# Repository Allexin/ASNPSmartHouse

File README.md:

**ЧЕРНОВИК**  
Uart Settings:  
Baud Rate: 19200  
Parity: No Parity  
Stop bit: One Stop  
Data Size: 8 bit  

Используемые типы:  
безнаковый байт - основной тип используемый в пакетах
строка - uint8_t длина строки, массив uint8_t[длина строки]

Структура команды:  
INFO  
ADDRESS  
DATA_LENGTH  
DATA  
CHECKSUM  

INFO - информация о пакете. Биты считаются справа налево.  
1 - бит четности(количество установленных битов должно быть четным)  
2 - бит приоритета(0 - отправляем если можем, 1 - отправляем всегда)  
3 - бит типа адреса(0 - персональный адрес, 1 - групповой адрес)  
4 - бит события(0 -  обычный пакет, 1 - событие)  
5,6,7.8 - не используются.  
ADDRESS - адрес устройства или группы, которому предназначается команда. 0x00 - броадкаст.  Если пакет является событием - адрес должен содержать собственный адрес устройства. Как будто он отправляет пакет самому себе.  
DATA_LENGTH - длина данных. Значение от 1 до 255.  
DATA - данные размером DATA_LENGTH  
CHECKSUM - простая чек сумма. Равняется сумме всех байт пакета, кроме самой чексуммы  

# Команды  
0x00 PING  
0x01 PONG  
0x02 LOG  
0x20 REQUEST_INFO  
0x21 RESPONSE_INFO  
0x22 GET_VARIABLES_COUNT  
0x23 RESPONSE_VARIABLES_COUNT  
0x24 GET_VARIABLES  
0x25 RESPONSE_VARIABLES  
0x26 GET_VARIABLES  
0x27 RESPONSE_VARIABLE  
0x28 SET_VARIABLE  
0x29 SUBSCRIBE_TO_VARIABLE  
0x2A EVENT_VARIABLE_CHANGED  

# Маршрутизация  
Широковещательные пакеты отправляются всем устройствам. Остальные пакеты отправляются только на устройства, у которых указан соответствующий адрес. Либо если пакет является событием - тем, кто подписался на адрес отправителя.
Любое устройство может подписаться на любые адреса. Подписаться в лоб на все 255 адресов плохая идея, сводящая на нет всю концепцию маршрутизации.  
Устройство должно отправить пакет подписки(PONG) при включении, а также при получении широковещательного пакета PING

# Системные пакеты
Широковещательные пакеты(адрес 0x00) с первым байтом данных равным 0 - являются системными пакетами и обрабатываются особым образом, зависящим от конкретного пакета.

# Специализированные пакеты
## Пакет PING
0x03 0x00 0x03 0x00 0x00 0x01 0x06  
Пакет с высоким приоритетом(0x03), широковещательный(0x00), 3 байт данных(0x03), служебные команды(0x00), команда PING(0x00), версия данных(0x01), контрольная сумма(0x06)  
При получении данного пакета устройство должно отправить пакет PONG  

## Пакет PONG
0x03 0x00 < data length> 0x00 0x01 0x01 < personal addresses count> < addresses> < group addresses count> < addresses> < subscribe addresses count> < addresses> < checksum>  
Пакет с высоким приоритетом(0x03), широковещательный(0x00), с данными размером(data length), служебные команды(0x00), команда PONG(0x01), версия данных(0x01), количество адресов устройств(personal addresses count), список адресов(addresses), количество адресов груп(group addresses count), список адресов(addresses), количество адресов подписок(subscribe addresses count), список адресов(addresses), контрольная сумма(checksum)  
Пакет содержит список адресов, пакеты для которых устройство желает получать.
personal addresses - адреса устойство(в том числе собственный адрес устройства)
group addresses - адреса групп, к которым устройство причесляет себя
subscribe addressed - адреса устройств, события с которых устройство будет получить
Если адресов больше, чем дозволяет размер протокола - допустимо отослать несколько пакетов.  
Первым адресом в списке всегда должен быть собственный адрес устройства.  
Пакет PONG должен отправляться с задержкой при включении устройства или при получении PING.  
Задержка должна быть равна 20мс * адрес устройства  
Протокол позволяет обрабатывать одновременное получение данных от множества источников, но буффер имеет ограниченный размер. Соответственно, если большое количество устройств одновременно откликнуться на PING или будут одновременно включены и сразу отправят PONG - часть пакетов может потеряться, что крайне не желательно в случае данного пакета.  

# Дополнительные пакеты
## Пакет REQUEST_INFO
0x03 < slave address> 0x04 0x00 0x20 0x01 < host address> < checksum>  
Пакет с высоким приоритетом(0x03), для устройства с адресом(slave address), 3 байта данных(0x04), служебные команды(0x00), команда REQUEST_INFO(0x20), версия данных(0x01), адрес отправителя(host address) контрольная сумма(checksum)  
При получении данного пакета, если адрес устройства соответствует переданному, устройство должно ответить пакетом INFO на адрес host address  

## Пакет RESPONSE_INFO
0x03 < host address> < data length> 0x00 0x21 0x01 < slave address> < device type length> < device type[]> < description length> < description[]> < checksum>  
Пакет с высоким приоритетом(0x03), для устройства с адресом(host address), данные длинной(data length), служебные команды(0x00), команда RESPONSE_INFO(0x21), версия данных(0x01), адрес отправителя(slave address), строка с типом устройства(str length, str[]), строка с описанием устройства(str length, str[]), контрольная сумма(checksum)  
В этом пакете устройство сообщает свой тип и дается краткое описание. Тип - строка без спецсимволов и пробелов, предназначенная для идентефикации устройства и подбора протокола для работы с ним. Описание не стандартизировано и может содержать любую информацию в любом виде(в том числе в бинарном).  

## Пакет LOG
0x03 0x00 <data length+3> 0x00 0x02 0x01 <data> 0x06  
Пакет с высоким приоритетом(0x03), широковещательный(0x00), data length+2 байт данных, служебные команды(0x00), команда LOG(0x02), версия данных(0x01), data - данные лога, контрольная сумма(0x06)  
data length не больше 200. Если в sendLog передать строку длиной больше 200 - она обрежется до этой длины.
Пакеты LOG отправляются устройством только если переменная LOG_ENABLE(uint8_t) больше 0. При каждом запуске устройства данная переменная уменьшается на 1.  Если мы хотим получать лог только до следующего перезапуска - прописываем 1. И после перезапуска отправка логов прекратится.

# Принципы управления устройством
Все взаимодействия между устройствами организуется через чтение и запись переменных.
Переменная может быть одного из трех видов:
1) config - переменная используется для настройки поведения и хранится в EEPROM
2) state - переменная определяет некое поведение устройства и хранится в RAM
3) command - переменная нигде не хранится и может быть только записана
Переменная может быть readonly, writeonly и readwrite

## Типы переменных
название-размер-enum index  
uint8_t	1 1			  
		uint8_t	1	беззнаковое целое  
uint16_t	2		2  
		uint16_t	2	беззнаковое целое  
ufixfloat16	2		3	  
		uint8_t	1	беззнаковая целая часть  
		uint8_t	1	беззнаковая дробная часть  
fixfloat16	2		4	  
		uint8_t	1	целая часть со знаком  
		uint8_t	1	беззнаковая дробная часть  
string16	16		5	  
		uint8_t[16]	16	строка длинной 16 символов. Если строка меньше 16 символов - остальные   символы забиваются нулями  
link	20			6  
		uint8_t	1	флаг адрес является групповым(1)  или персональным(0)  
		uint8_t	1	адрес устройства  
		string16	16	название поля  
		uint8_t	1	номер слота  
		uint8_t	1	ожидаемый тип(для валидации)  

#Пакеты управления переменными

## Пакет GET_VARIABLES_COUNT  
Запрашивает количество всех переменных, которые доступны для внешнего доступа у устройства  
0x03 < device address> 0x04 0x00 0x22 0x01 < self address> < checksum>  
Пакет с высоким приоритетом(0x03), для устройства с адресом(device address), 4 байта данных(0x04), служебные команды(0x00), команда GET_VARIABLES_COUNT(0x22), версия данных(0x01), адрес отправителя(self address) контрольная сумма(checksum)  
  
## Пакет RESPONSE_VARIABLES_COUNT  
Возвращает количество переменных, которые доступны для внешнего доступа у устройства  
0x03 < device address> 0x05 0x00 0x23 0x01 < self address> < count> < checksum>  
Пакет с высоким приоритетом(0x03), для устройства с адресом(device address), 5 байт данных(0x05), служебные команды(0x00), команда RESPONSE_VARIABLES_COUNT(0x23), версия данных(0x01), адрес отправителя(self address), количество переменных(count), контрольная сумма(checksum)  

## Пакет GET_VARIABLES  
Запрашивает подробную информацию о переменных, начиная с определенной  
0x03 < device address> 0x05 0x00 0x24 0x01 < self address> < start index> < checksum>  
Пакет с высоким приоритетом(0x03), для устройства с адресом(device address), 5 байт данных(0x05), служебные команды(0x00), команда GET_VARIABLES(0x24), версия данных(0x01), адрес отправителя(self address), переменная начиная с которой нужно отправлять переменные(start index), контрольная сумма(checksum)  
  
## Пакет RESPONSE_VARIABLES  
Возвращает подробную информацию о переменных, начиная с запрошенной и заканчивая последней(или столько, сколько уместится в пакет)  
0x03 < device address> < data length> 0x00 0x25 0x01 < self address> < start index> < last index> [ variables] < checksum>  
Пакет с высоким приоритетом(0x03), для устройства с адресом(device address), размер данных(data length), служебные команды(0x00), команда RESPONSE_VARIABLES(0x25), версия данных(0x01), адрес отправителя(self address), первая переменная в списке(start index), последняя переменная в списке(last index), список переменных в формате variable_info [ variables],контрольная сумма(checksum)  
  
## Пакет GET_VARIABLE  
Запрашивает значение переменной  
0x03/0x06 < device/group address> < data length> 0x00 0x26 0x01 < self address> < variable_info> < checksum>  
Пакет с высоким приоритетом(0x03 или 0x06), для устройства с адресом(device/group address), размер данных(data length), служебные команды(0x00), команда GET_VARIABLES(0x26), версия данных(0x01), адрес отправителя(self address), переменная (variable_info)(вместо количества слотов содержит индекс слота из которого следует прочитать значение),контрольная сумма(checksum)  
  
## Пакет RESPONSE_VARIABLE  
Запрашивает значение переменной  
0x03 < device address> < data length> 0x00 0x27 0x01 < self address> < variable_info> < variable> < checksum>  
Пакет с высоким приоритетом(0x03), для устройства с адресом(device address), размер данных(data length), служебные команды(0x00), команда RESPONSE_VARIABLE(0x27), версия данных(0x01), адрес отправителя(self address), переменная (variable_info)(вместо количества слотов содержит индекс слота из которого прочитано значение), содержимое переменное в зависимости от типа(variable),контрольная сумма(checksum)  
  
## Пакет SET_VARIABLE  
Устанавливает значение переменной  
0x03 < device address> < data length> 0x00 0x28 0x01 < variable_info> < variable> < checksum>  
Пакет с высоким приоритетом(0x03), для устройства с адресом(device address), размер данных(data length), служебные команды(0x00), команда SET_VARIABLE(0x28), версия данных(0x01), переменная (variable_info)(вместо количества слотов содержит индекс слота в который следует установить значение), содержимое переменное в зависимости от типа(variable),контрольная сумма(checksum)  
  
## Пакет SUBSCRIBE_TO_VARIABLE  
Запрашивает/отменяет подписку на изменение переменной  
0x03/0x06 < device/group address> < data length> 0x00 0x29 0x01 < variable_info> < subscribe> < priority> < checksum>  
Пакет с высоким приоритетом(0x03/0x06), для устройства с адресом(device/group address), размер данных(data length), служебные команды(0x00), команда SUBSCRIBE_TO_VARIABLE(0x29), версия данных(0x01), переменная (variable_info), флаг подписки(1) или отписки(0)(<subscribe>), флаг важности подписки(priority), контрольная сумма(checksum)  
  
## Пакет EVENT_VARIABLE_CHANGED  
Информирование подписчиков о том, что переменная была изменена  
Приоритет выбирается на основе запросов подспичиков, если есть хотя бы один кто хочет максимальный приоритет - шлется по максимуму.
< package_info> < device address> < data length> 0x00 0x2A 0x01 < variable_info> < variable> < checksum>  
Пакет события с приоритетом в зависимости от подписки(package_info), адрес устройства(device address), размер данных(data length), служебные команды(0x00), версия данных(0x01), команда EVENT_VARIABLE_CHANGED(0x2A), переменная (variable_info)(вместо количества слотов содержит индекс изменившегося слота), содержимое переменной(variable),контрольная сумма(checksum)  
  
### Описание структуры variable_info  
string16 - название переменной
uint8_t - тип переменной
uint8_t - количество слотов в переменной(количество элементов в массиве)

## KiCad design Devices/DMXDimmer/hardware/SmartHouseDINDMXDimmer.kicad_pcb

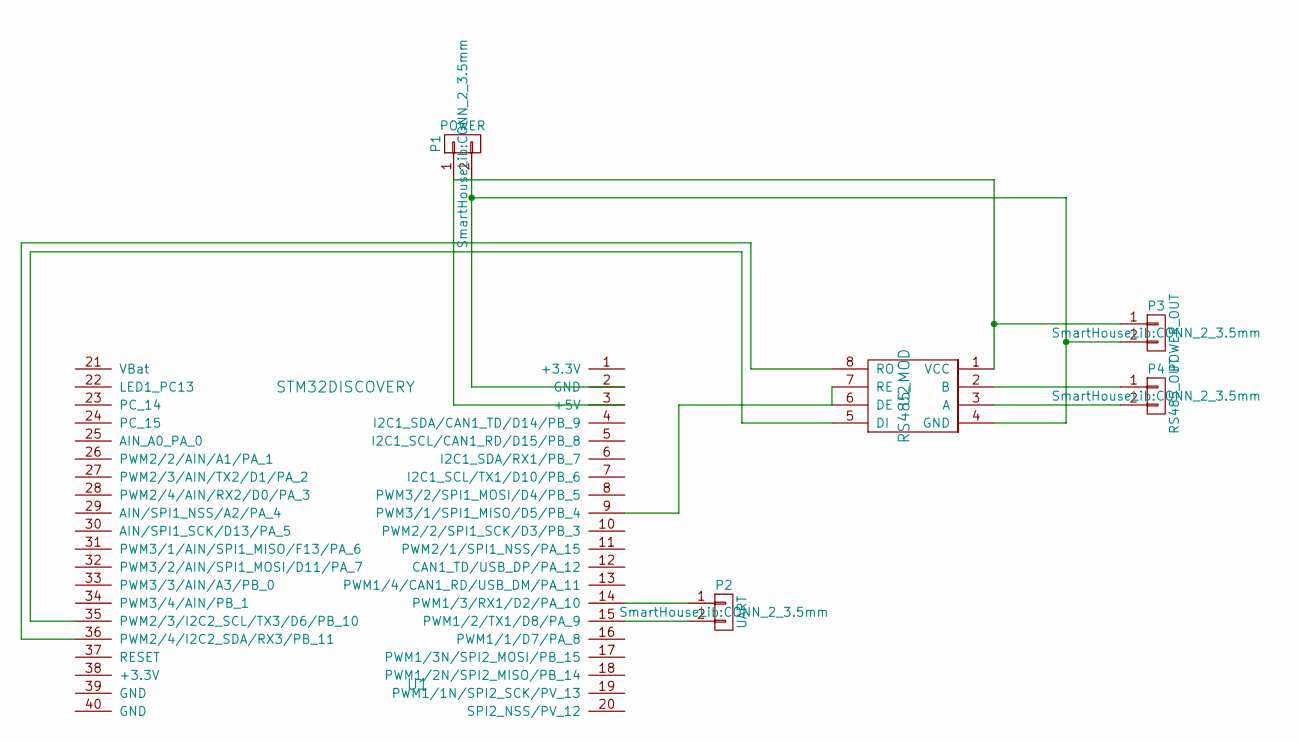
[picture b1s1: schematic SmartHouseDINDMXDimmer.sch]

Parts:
P1: POWER; CONN_2_3.5mm
P2: UART; CONN_2_3.5mm
P3: POWER_OUT; CONN_2_3.5mm
P4: RS485_OUT; CONN_2_3.5mm
U1: STM32DISCOVERY; STM32_DISCOVERY
U2: RS485_MOD; RS485

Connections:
unnamed: P1.1, P3.1, U1.3 (+5V), U2.1 (VCC)
unnamed: P1.2, P3.2, U1.2 (GND), U2.4 (GND)
unnamed: P2.1, U1.14 (PWM1/3/RX1/D2/PA_10)
unnamed: P2.2, U1.15 (PWM1/2/TX1/D8/PA_9)
unnamed: P4.1, U2.2 (B)
unnamed: P4.2, U2.3 (A)
unnamed: U1.9 (PWM3/1/SPI1_MISO/D5/PB_4), U2.6 (DE), U2.7 (RE)
unnamed: U1.35 (PWM2/3/I2C2_SCL/TX3/D6/PB_10), U2.5 (DI)
unnamed: U1.36 (PWM2/4/I2C2_SDA/RX3/PB_11), U2.8 (RO)

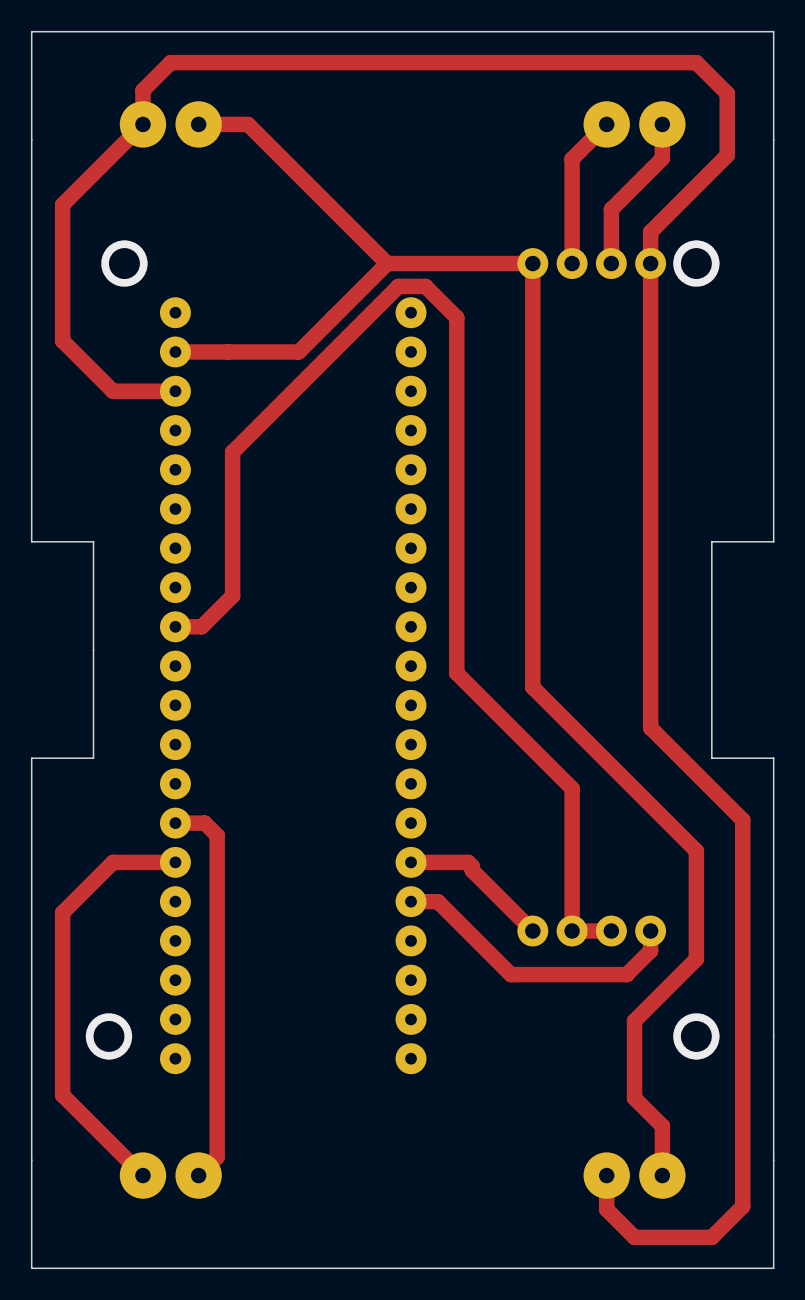
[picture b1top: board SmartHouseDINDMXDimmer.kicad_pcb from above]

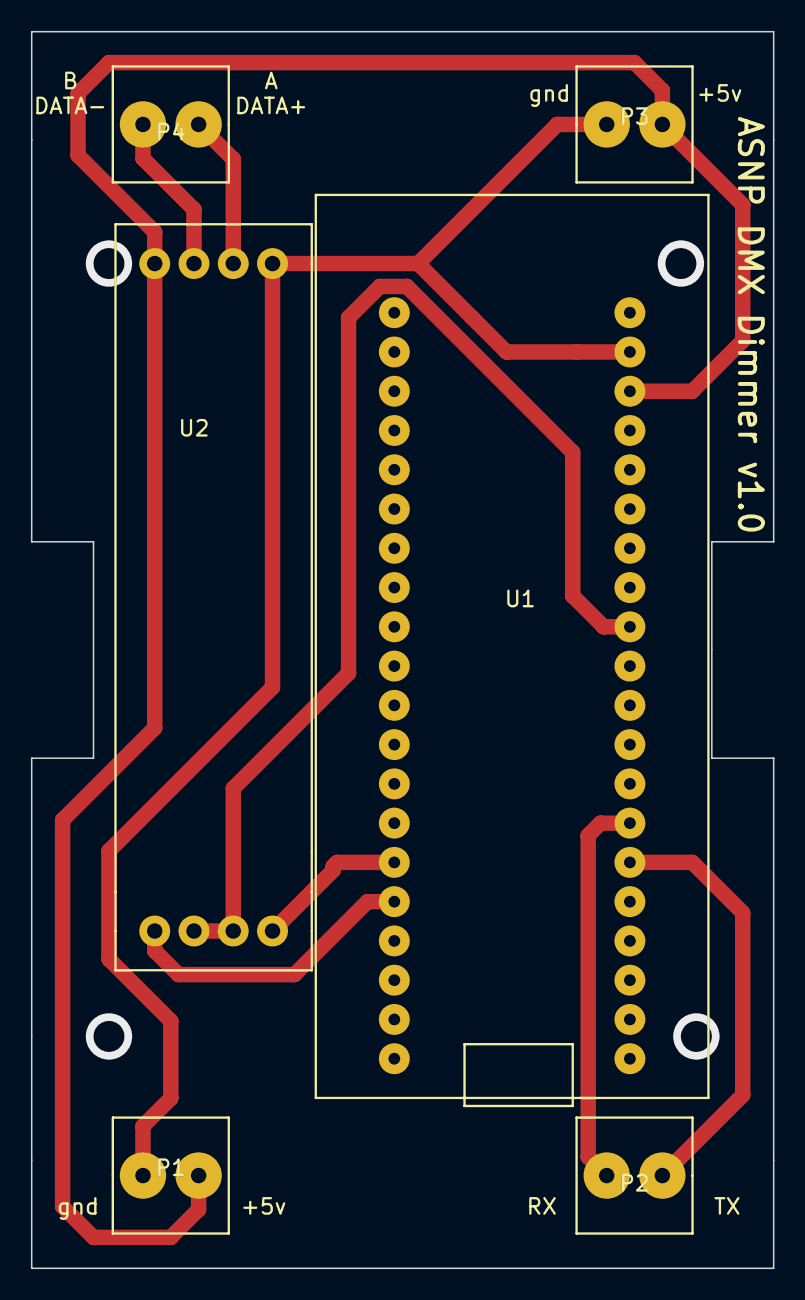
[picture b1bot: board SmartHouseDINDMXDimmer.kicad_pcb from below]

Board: 2 copper layers, 48.0 x 80.0 mm, 6 parts (6 on the bottom side), 9 nets.

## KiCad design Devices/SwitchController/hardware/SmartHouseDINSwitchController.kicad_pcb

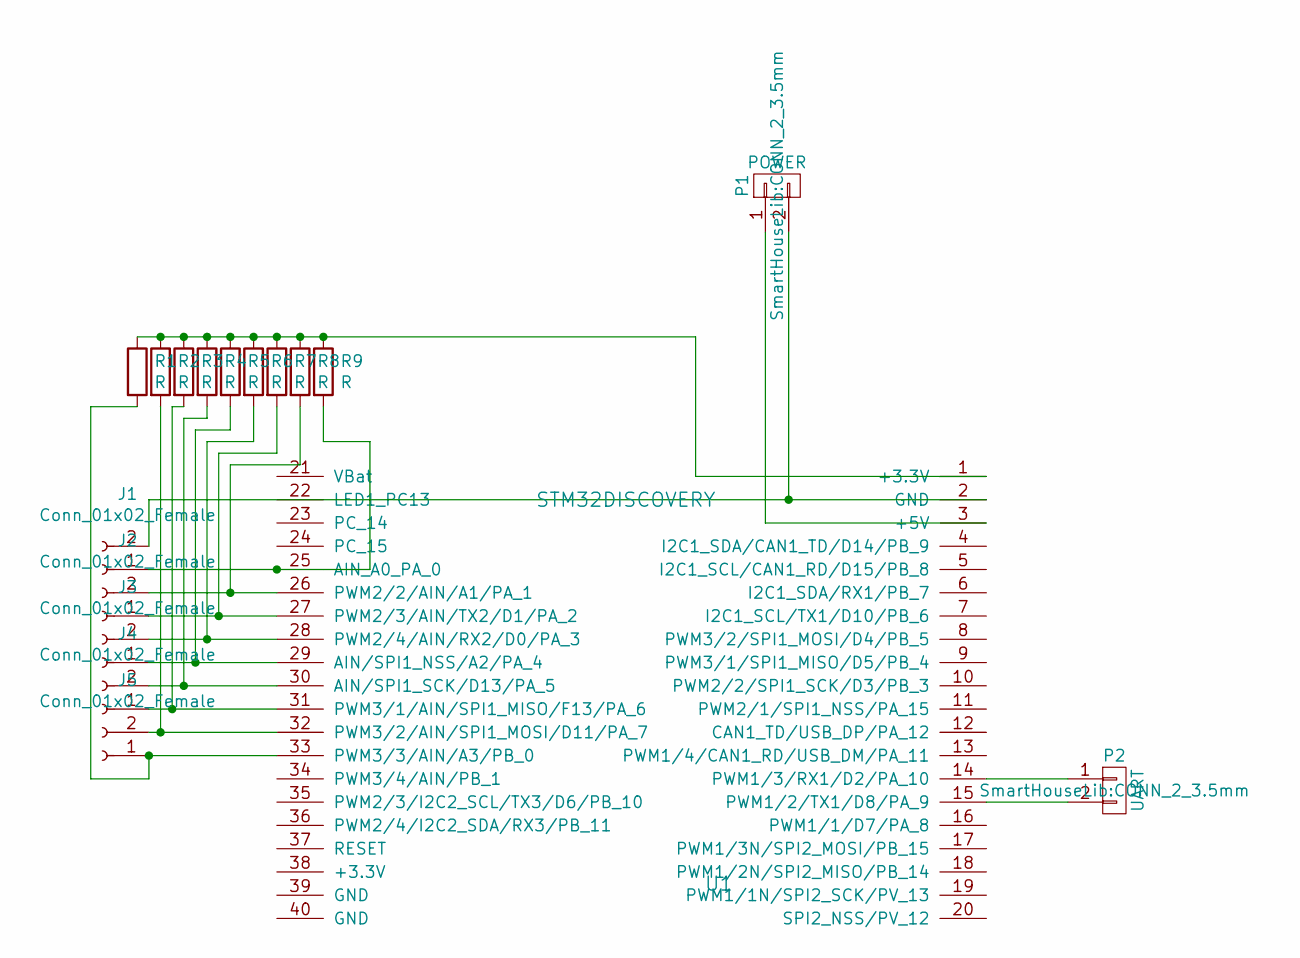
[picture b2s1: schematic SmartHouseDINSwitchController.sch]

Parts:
J1, J2, J3, J4, J5: Conn_01x02_Female; CONN_2_3.5mm
P1: POWER; CONN_2_3.5mm
P2: UART; CONN_2_3.5mm
R1, R2, R3, R4, R5, R6, R7, R8, R9: R; R_1206_3216Metric_Pad1.42x1.75mm_HandSolder
U1: STM32DISCOVERY; STM32_DISCOVERY

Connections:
unnamed: J1.1, R9.2, U1.25 (AIN_A0_PA_0)
unnamed: J1.2, P1.2, U1.2 (GND)
unnamed: J2.1, R7.2, U1.27 (PWM2/3/AIN/TX2/D1/PA_2)
unnamed: J2.2, R8.2, U1.26 (PWM2/2/AIN/A1/PA_1)
unnamed: J3.1, R5.2, U1.29 (AIN/SPI1_NSS/A2/PA_4)
unnamed: J3.2, R6.2, U1.28 (PWM2/4/AIN/RX2/D0/PA_3)
unnamed: J4.1, R3.2, U1.31 (PWM3/1/AIN/SPI1_MISO/F13/PA_6)
unnamed: J4.2, R4.2, U1.30 (AIN/SPI1_SCK/D13/PA_5)
unnamed: J5.1, R1.2, U1.33 (PWM3/3/AIN/A3/PB_0)
unnamed: J5.2, R2.2, U1.32 (PWM3/2/AIN/SPI1_MOSI/D11/PA_7)
unnamed: P1.1, U1.3 (+5V)
unnamed: P2.1, U1.14 (PWM1/3/RX1/D2/PA_10)
unnamed: P2.2, U1.15 (PWM1/2/TX1/D8/PA_9)
unnamed: R1.1, R2.1, R3.1, R4.1, R5.1, R6.1, R7.1, R8.1, R9.1, U1.1 (+3.3V)

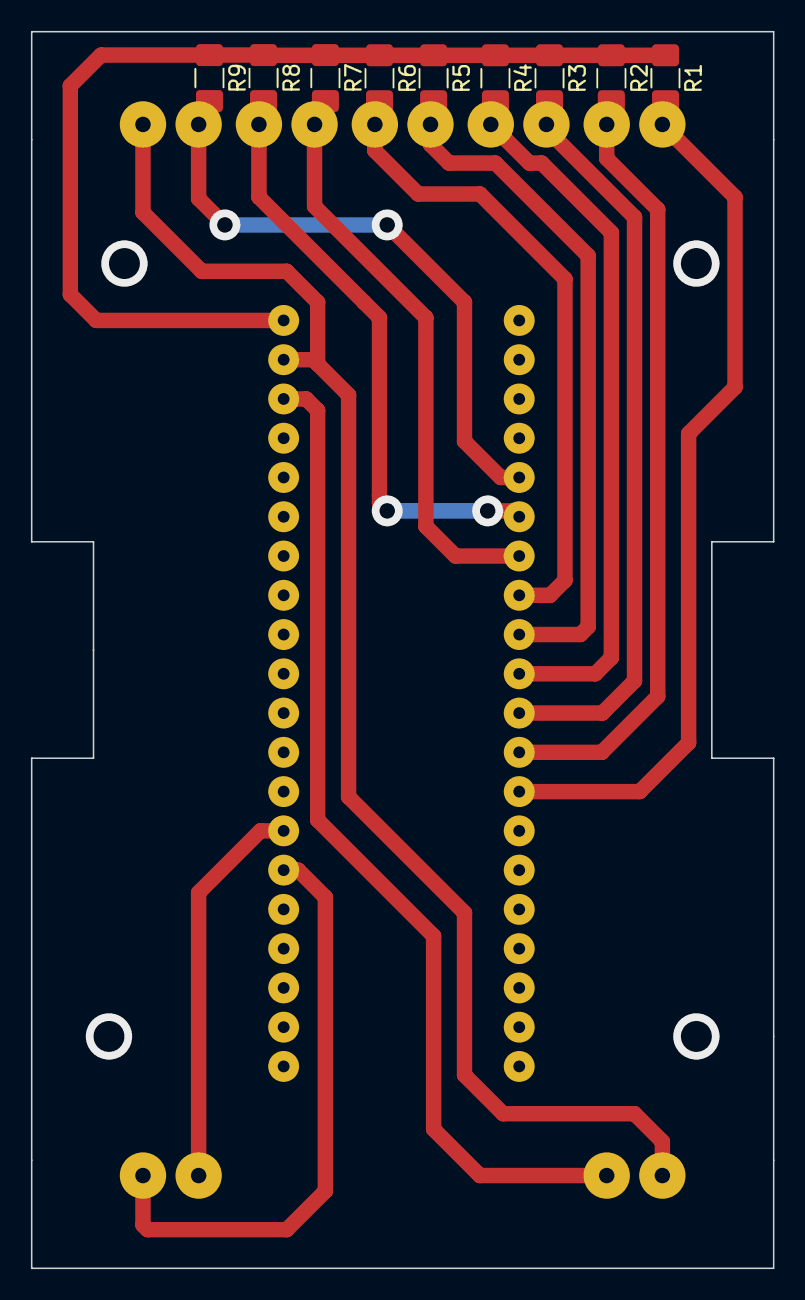
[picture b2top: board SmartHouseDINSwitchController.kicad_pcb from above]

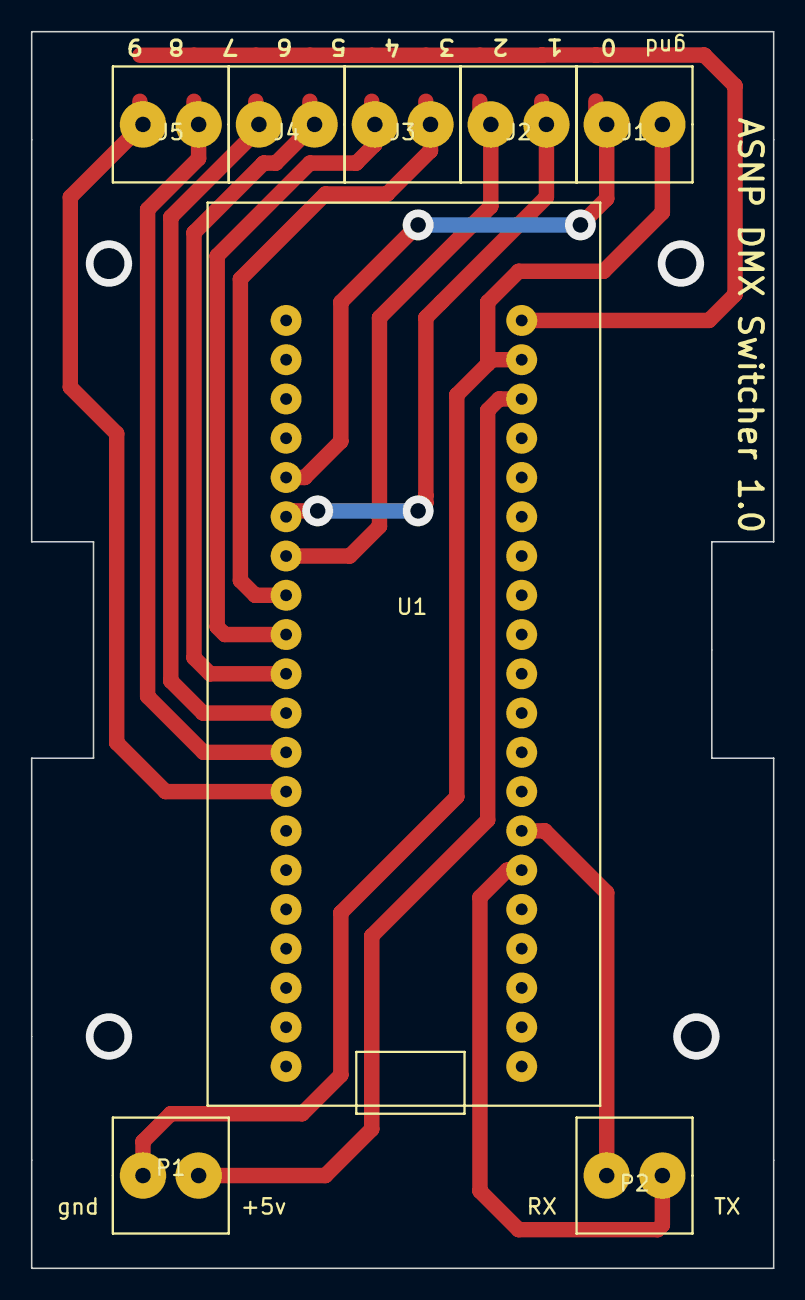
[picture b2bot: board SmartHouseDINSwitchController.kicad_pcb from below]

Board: 2 copper layers, 48.0 x 80.0 mm, 17 parts (8 on the bottom side), 14 nets.

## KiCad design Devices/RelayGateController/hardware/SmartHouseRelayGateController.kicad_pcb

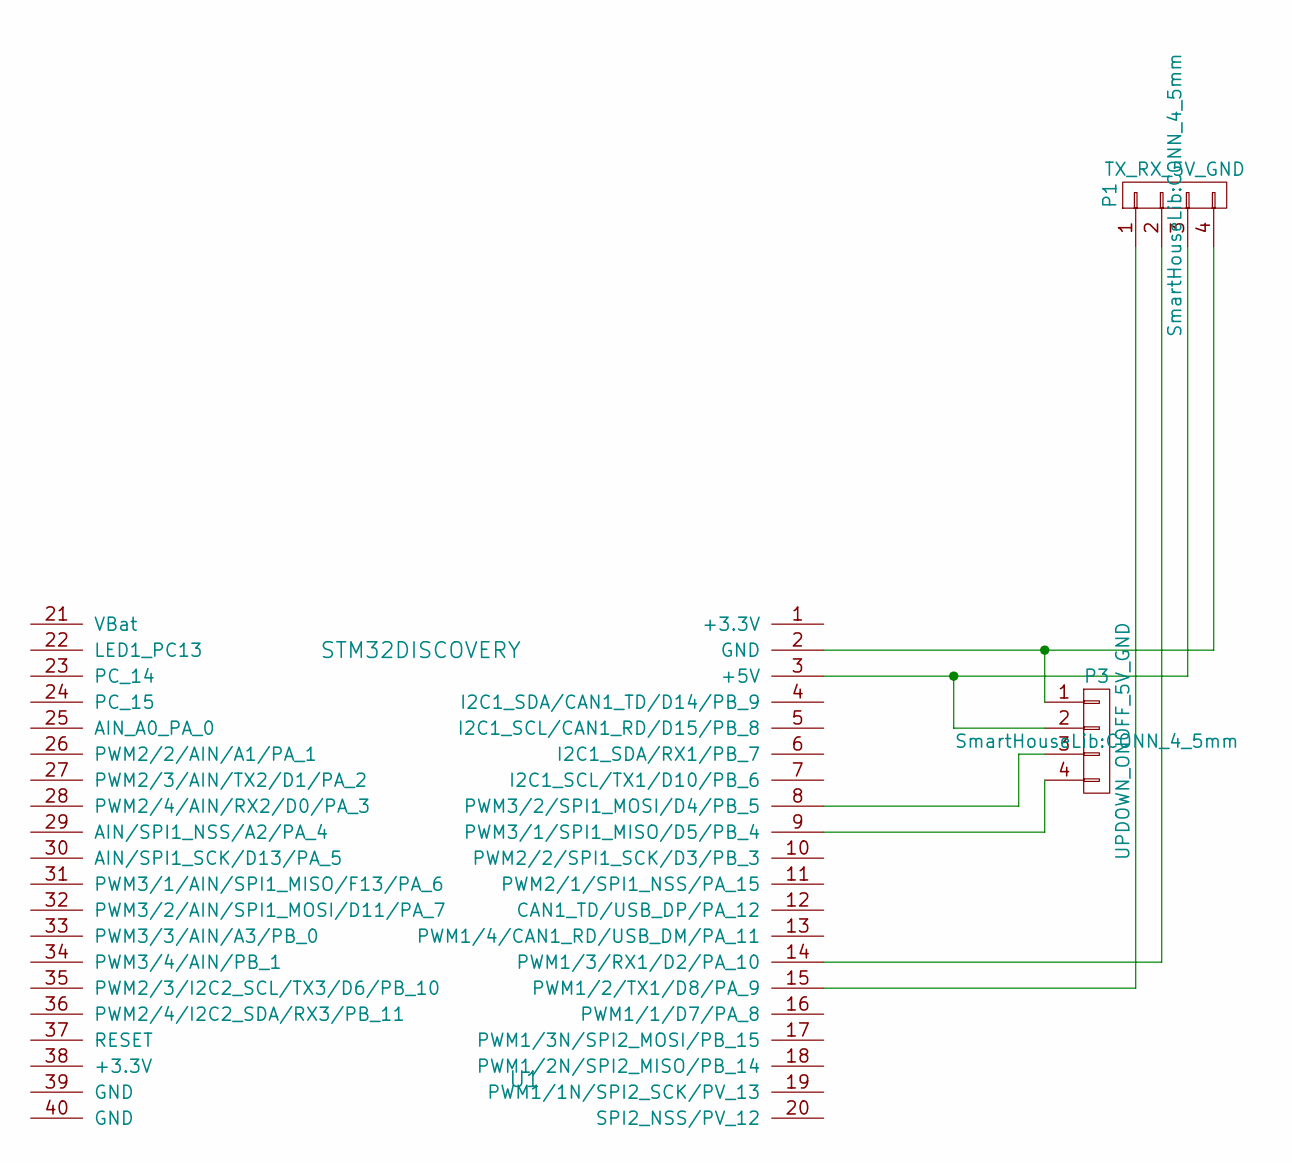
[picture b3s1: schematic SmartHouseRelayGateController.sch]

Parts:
P1: TX_RX_5V_GND; CONN_4_5mm
P3: UPDOWN_ONOFF_5V_GND; CONN_4_5mm
U1: STM32DISCOVERY; STM32_DISCOVERY

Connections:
unnamed: P1.1, U1.15 (PWM1/2/TX1/D8/PA_9)
unnamed: P1.2, U1.14 (PWM1/3/RX1/D2/PA_10)
unnamed: P1.3, P3.2, U1.3 (+5V)
unnamed: P1.4, P3.1, U1.2 (GND)
unnamed: P3.3, U1.8 (PWM3/2/SPI1_MOSI/D4/PB_5)
unnamed: P3.4, U1.9 (PWM3/1/SPI1_MISO/D5/PB_4)

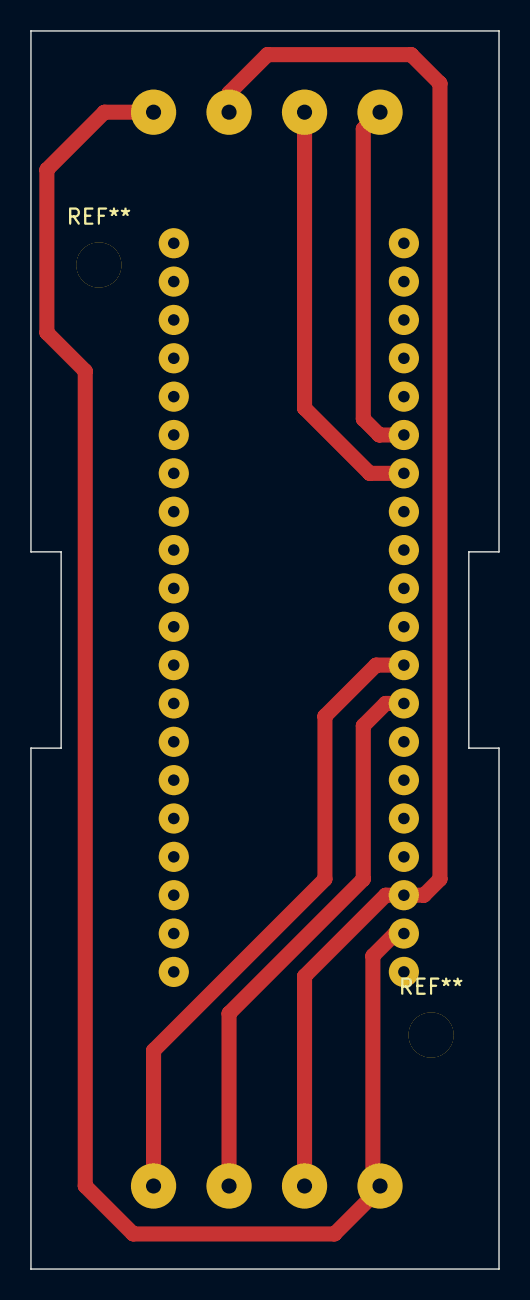
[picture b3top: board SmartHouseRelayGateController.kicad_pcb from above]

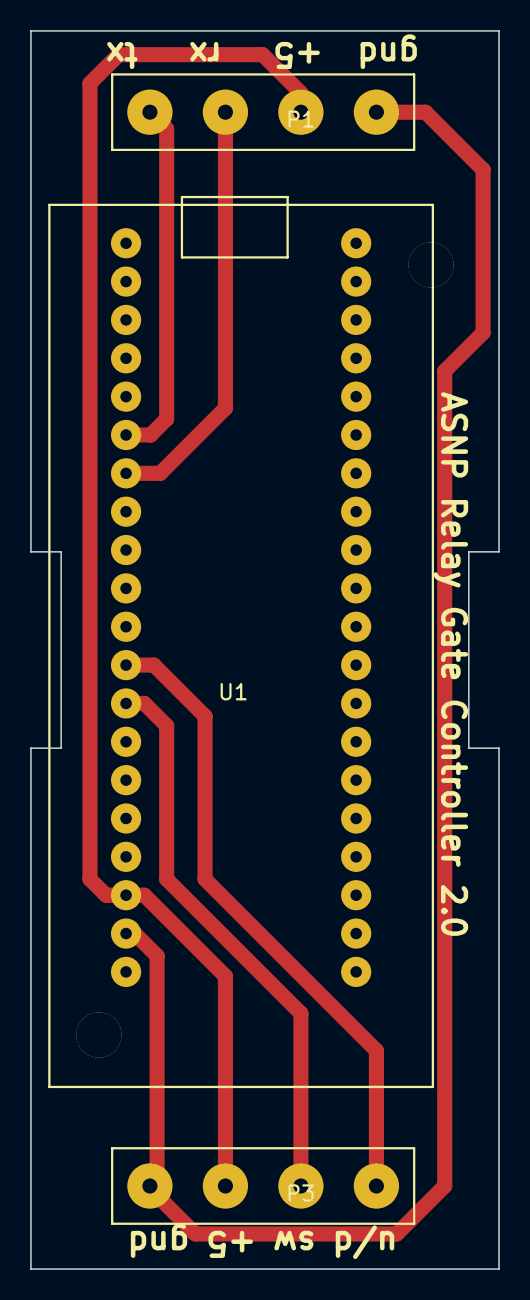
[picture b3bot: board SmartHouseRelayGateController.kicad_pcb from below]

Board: 2 copper layers, 31.0 x 82.0 mm, 3 parts (3 on the bottom side), 6 nets.

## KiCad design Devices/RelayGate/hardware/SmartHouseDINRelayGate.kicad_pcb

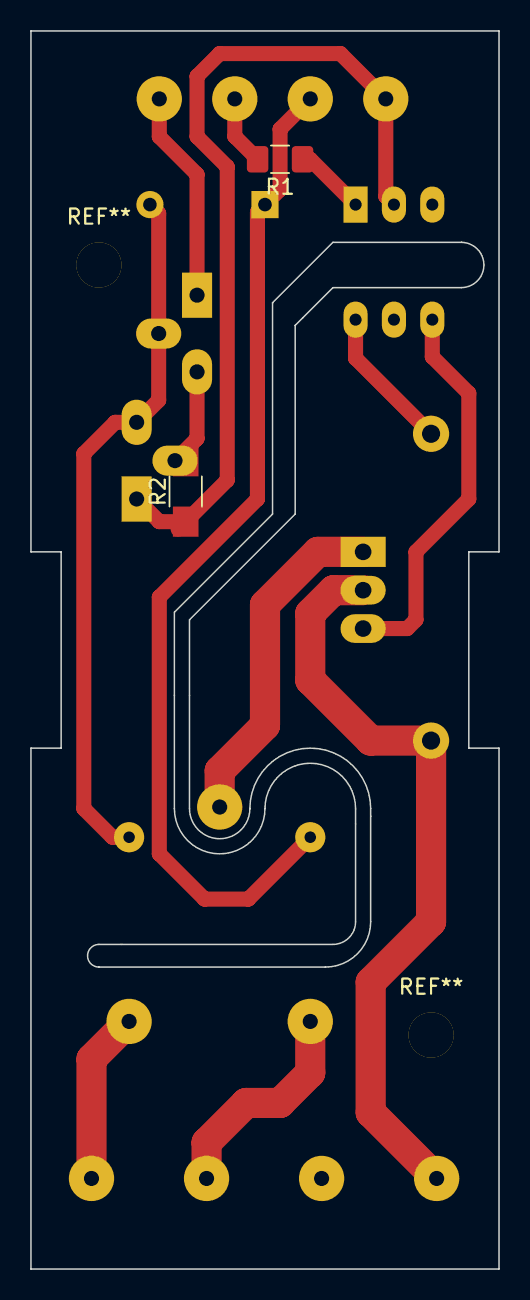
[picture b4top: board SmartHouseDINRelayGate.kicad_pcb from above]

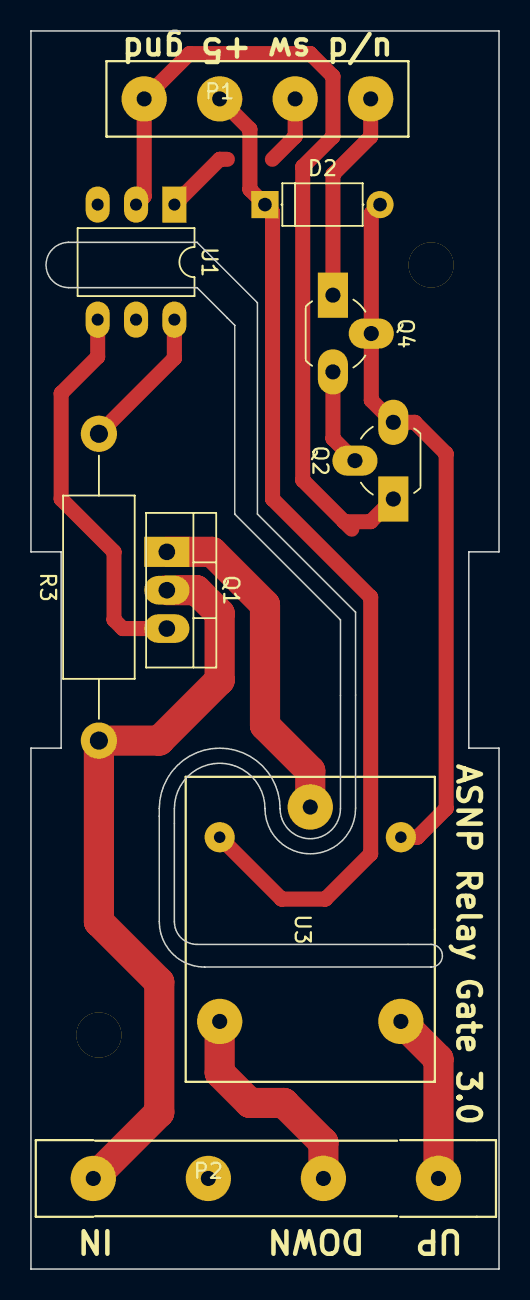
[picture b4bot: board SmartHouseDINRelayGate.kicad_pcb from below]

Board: 2 copper layers, 31.0 x 82.0 mm, 11 parts (9 on the bottom side), 13 nets.

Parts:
D2: D; D_A-405_P7.62mm_Horizontal
P1: CONN_UPDOWN_ONOFF_PWR_GND; CONN_4_5mm
P2: CONN_IN_DOWN_UP; CONN_4_7.62mm
Q1: BTA16-600B; TO-220-3_Vertical
Q2: Q_NPN_EBC; TO-92_Rugged
Q4: Q_NPN_BCE_DTC124; TO-92_Rugged
R1: R; R_1206_3216Metric_Pad1.42x1.75mm_HandSolder
R2: R4K7; R_1206_HandSoldering
R3: R; R_Axial_DIN0414_L11.9mm_D4.5mm_P20.32mm_Horizontal
U1: MOC3020M; DIP-6_W7.62mm_LongPads
U3: RELAY_1C; RELAY_TRU_1C

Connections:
unnamed: D2.1, P1.3, U3.2
unnamed: D2.2, Q2.3, Q4.2, U3.1
unnamed: P1.1, Q4.1
unnamed: P1.2, R1.2
unnamed: P1.4, Q2.1, R2.1, U1.2
unnamed: P2.1, U3.4
unnamed: P2.2, U3.5
unnamed: P2.4, Q1.2, R3.1
unnamed: Q1.1, U3.3
unnamed: Q1.3, U1.4
unnamed: Q2.2, Q4.3, R2.2
unnamed: R1.1, U1.1
unnamed: R3.2, U1.6

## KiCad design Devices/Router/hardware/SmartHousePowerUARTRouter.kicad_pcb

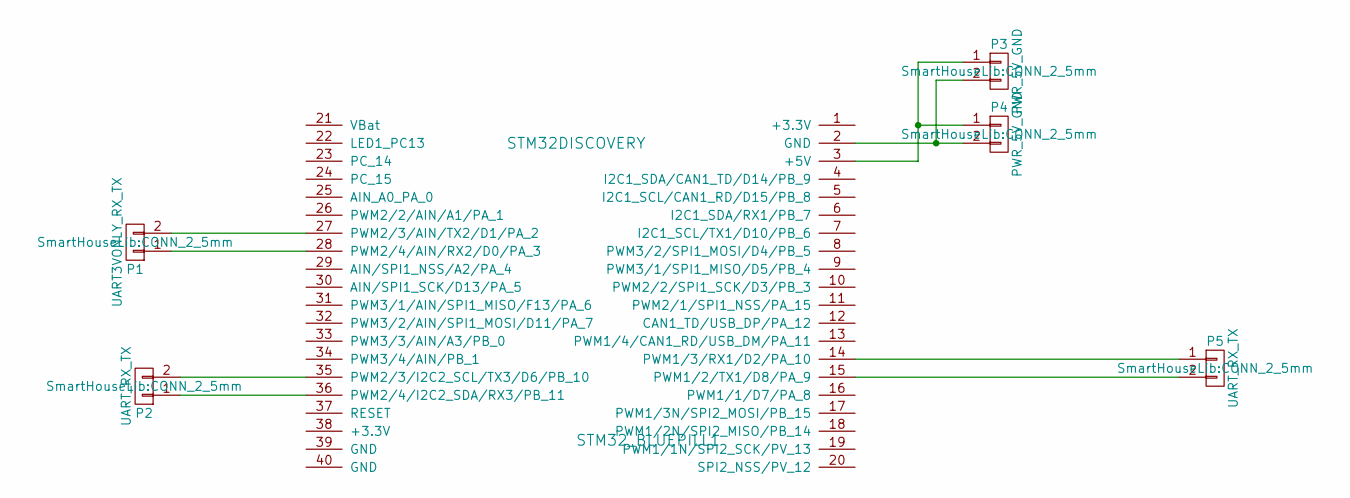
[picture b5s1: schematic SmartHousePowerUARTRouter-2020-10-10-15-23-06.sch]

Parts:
P1: UART3VONLY_RX_TX; CONN_2_5mm
P2, P5: UART_RX_TX; CONN_2_5mm
P3, P4: PWR_5V_GND; CONN_2_5mm
STM32_BLUEPILL1: STM32DISCOVERY; STM32_DISCOVERY

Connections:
unnamed: P1.1, STM32_BLUEPILL1.28 (PWM2/4/AIN/RX2/D0/PA_3)
unnamed: P1.2, STM32_BLUEPILL1.27 (PWM2/3/AIN/TX2/D1/PA_2)
unnamed: P2.1, STM32_BLUEPILL1.36 (PWM2/4/I2C2_SDA/RX3/PB_11)
unnamed: P2.2, STM32_BLUEPILL1.35 (PWM2/3/I2C2_SCL/TX3/D6/PB_10)
unnamed: P3.1, P4.1, STM32_BLUEPILL1.3 (+5V)
unnamed: P3.2, P4.2, STM32_BLUEPILL1.2 (GND)
unnamed: P5.1, STM32_BLUEPILL1.14 (PWM1/3/RX1/D2/PA_10)
unnamed: P5.2, STM32_BLUEPILL1.15 (PWM1/2/TX1/D8/PA_9)

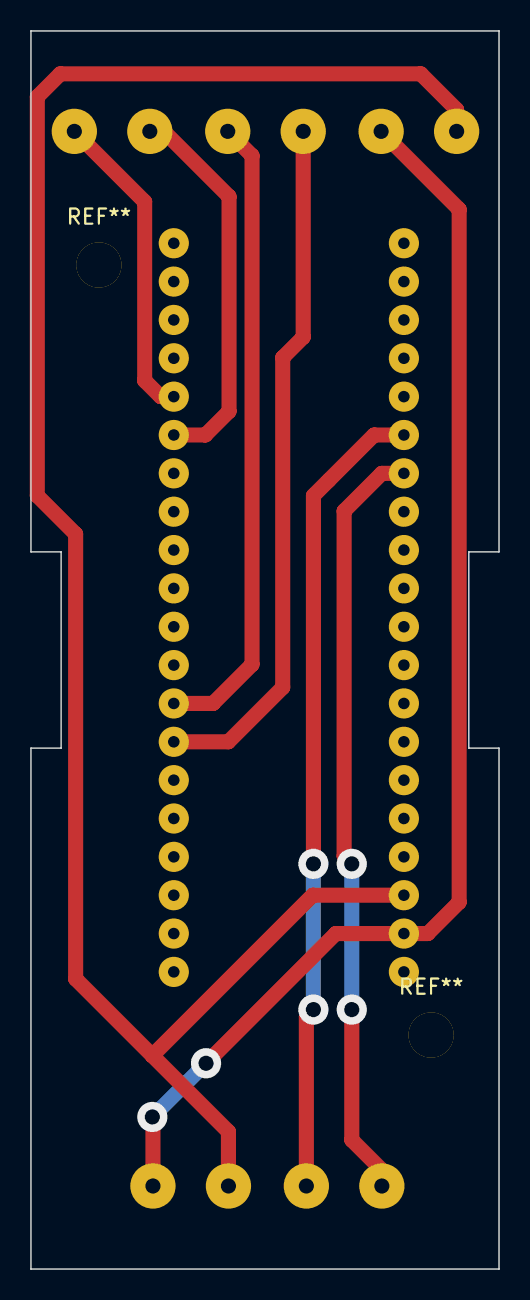
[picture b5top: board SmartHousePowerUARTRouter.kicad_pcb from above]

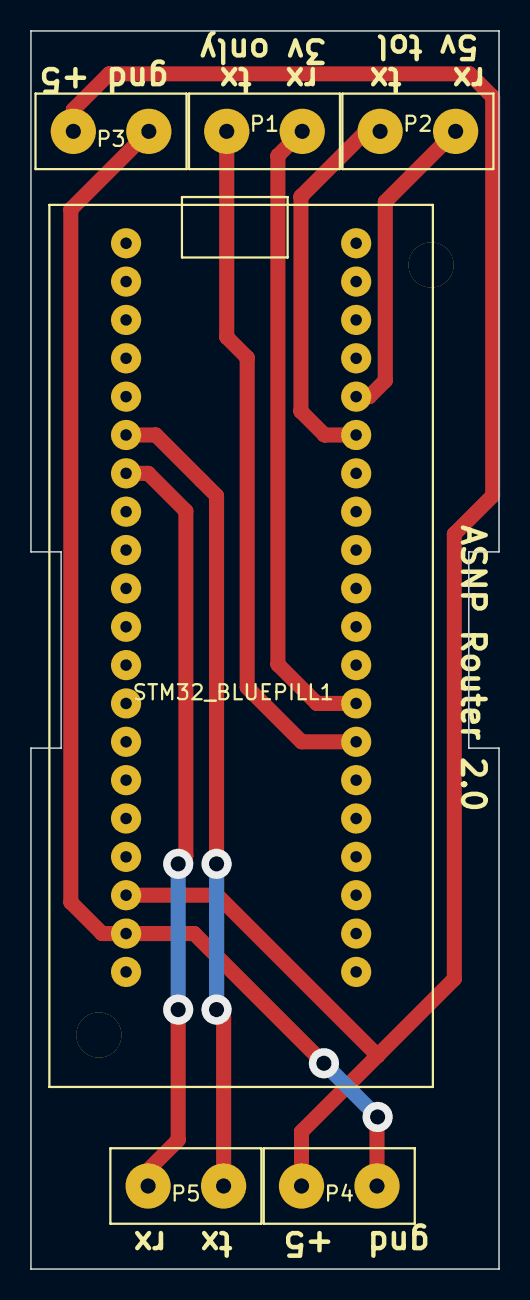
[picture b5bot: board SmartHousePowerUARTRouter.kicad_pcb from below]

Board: 2 copper layers, 31.0 x 82.0 mm, 6 parts (6 on the bottom side), 8 nets.

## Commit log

2019-12-01 -Initial commit
2019-12-01 -Refactoring -Convert ASNP Protocol to Arduino Library
2019-12-18 -Total ASNP Remote Controller refactoring
2021-02-27 -Voice control initial commit
2021-03-14 -add size for uint8 vector4
2021-03-14 -add uint8 vector4 type
2021-03-14 -remove group addressed behaviour: merge private addressed with group. now group address is just addition addresses
2021-03-14 -add new avriables type editors -small improvements
2021-03-14 -android software for remote control. Alpha version WIP(hardcoded devices, no settings)
2021-03-14 -Devices updates
